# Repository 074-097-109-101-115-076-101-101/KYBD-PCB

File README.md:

# KYBD-PCB

### • ATMEGA32U4-AUR
### • Adafruit 5050 RGB LED with Integrated Driver Chip
### • USB C Port
### • Rotary Encoder
### • SRVO5-4
### • OLED Display
### • Crystal Oscillator

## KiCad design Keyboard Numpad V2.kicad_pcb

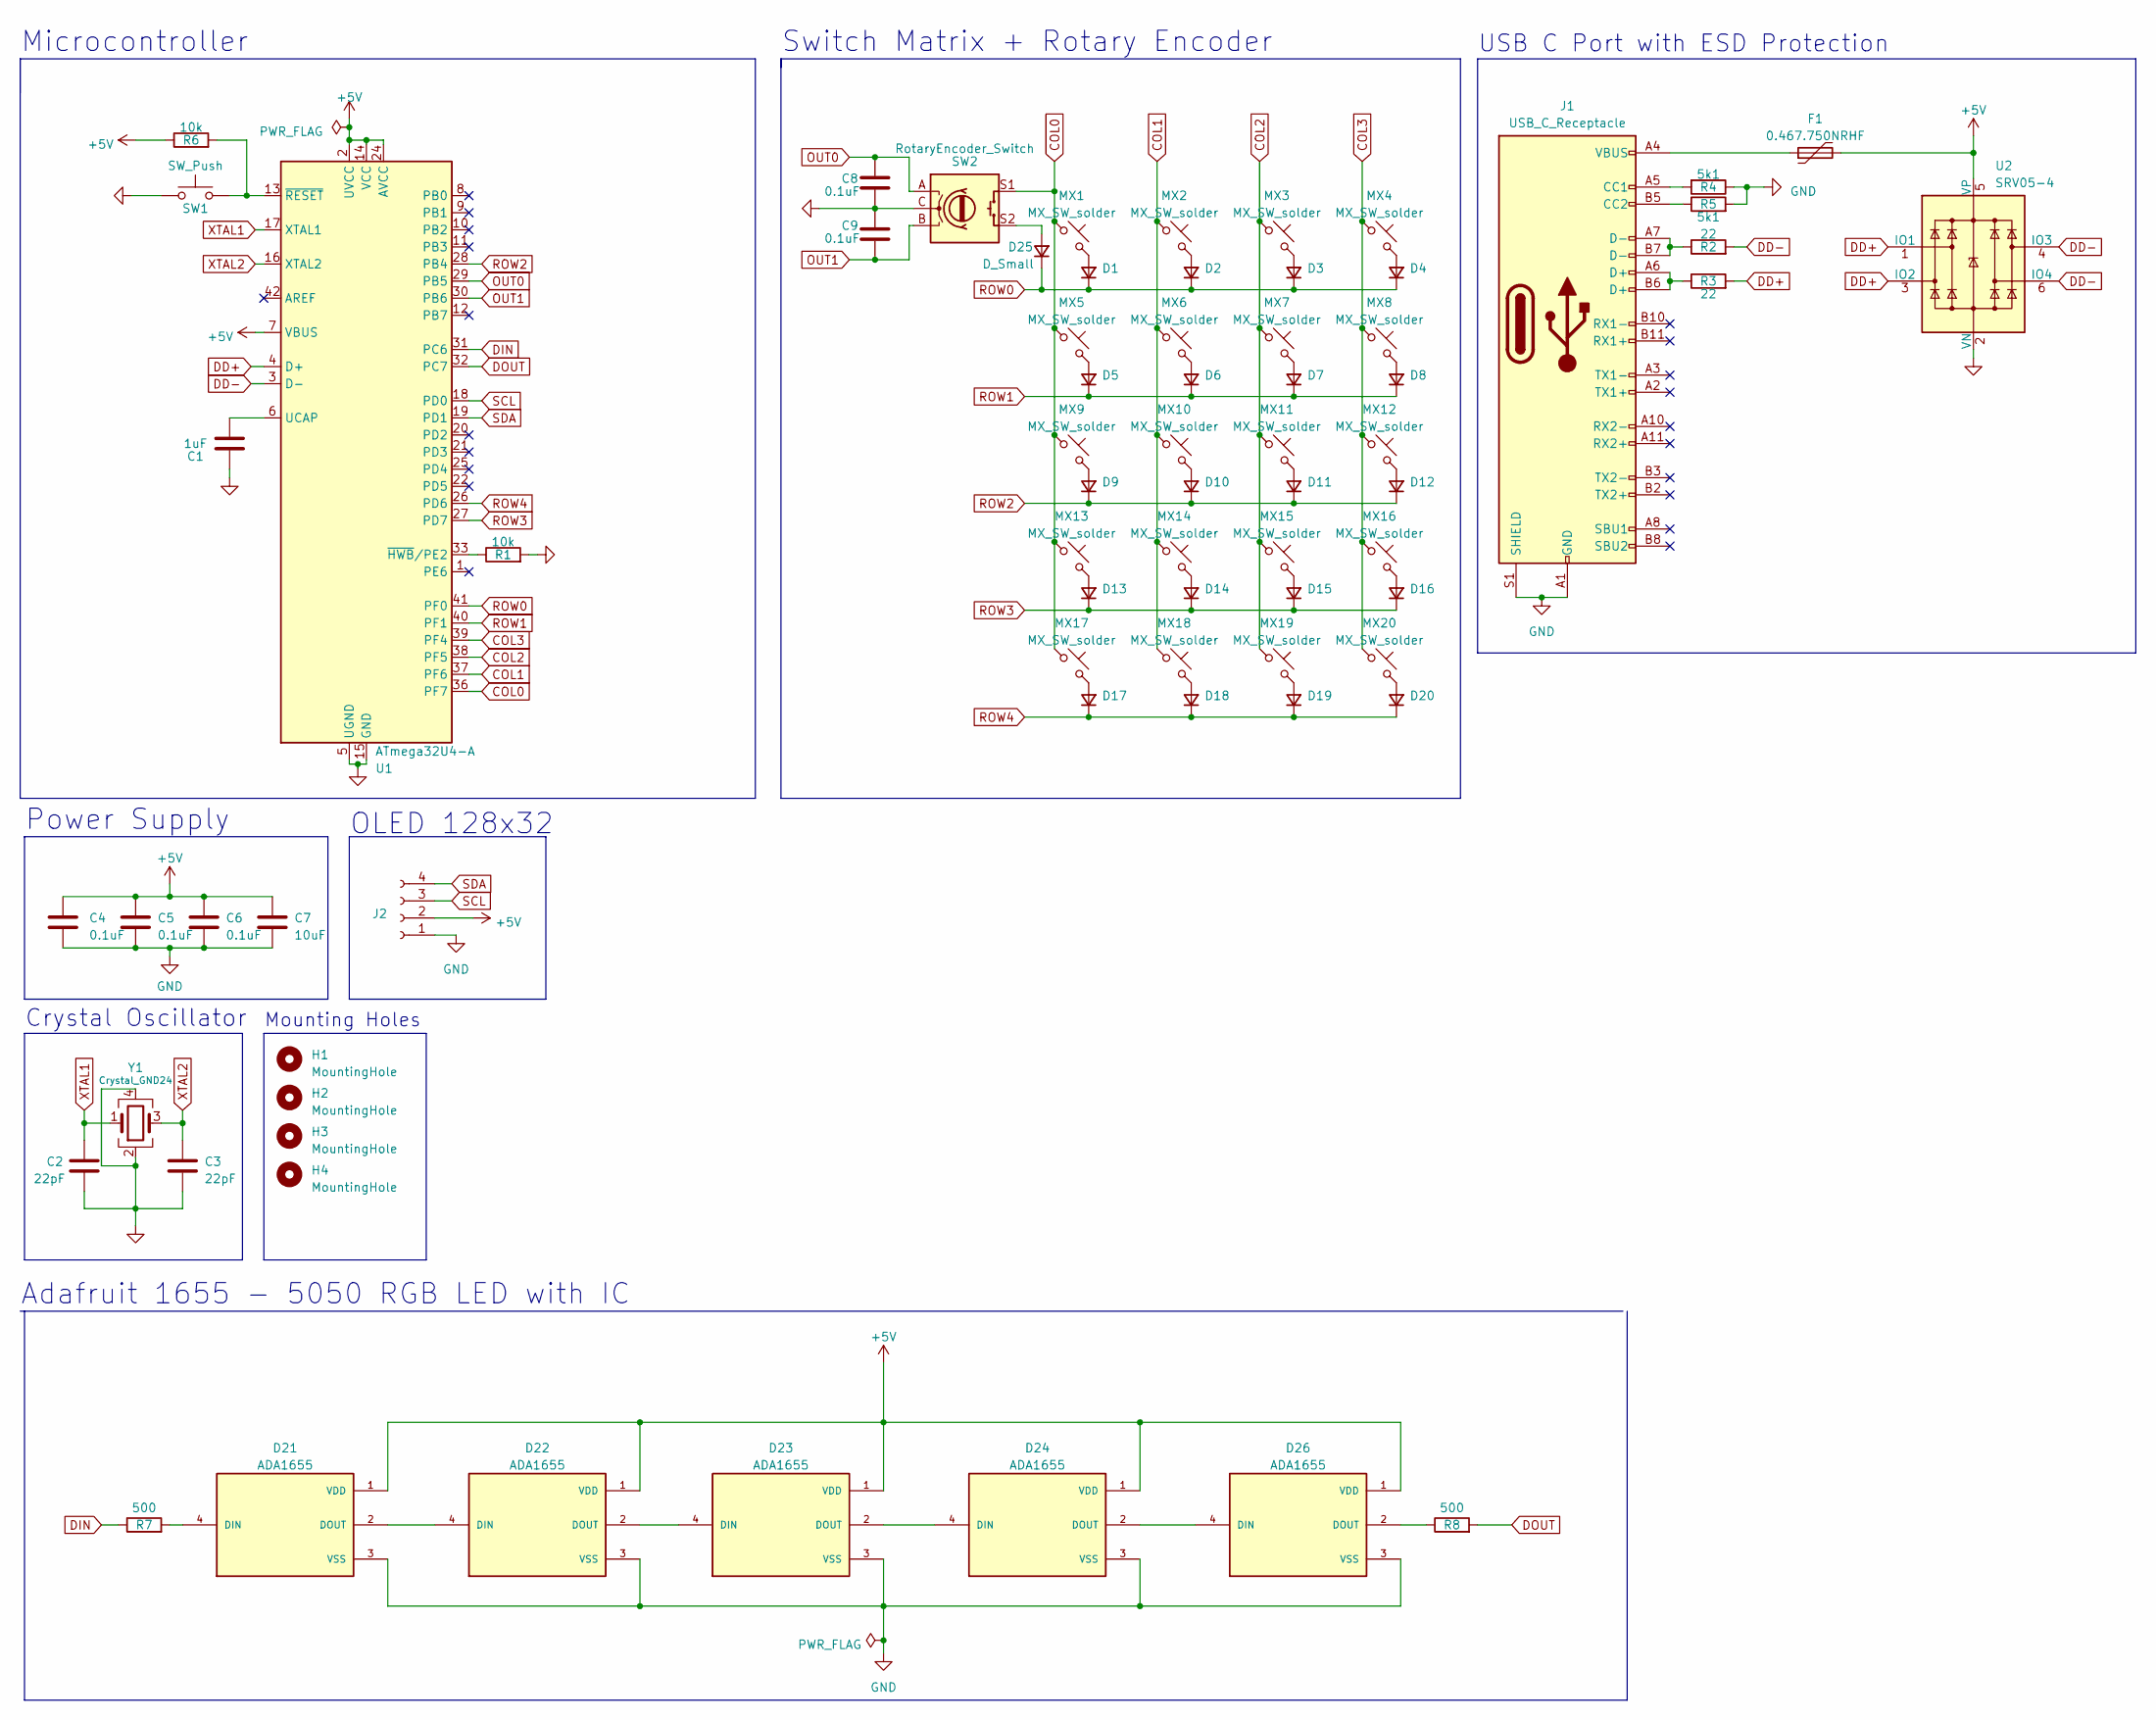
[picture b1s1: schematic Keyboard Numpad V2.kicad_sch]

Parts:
C1: 1uF; C_0805_2012Metric
C2, C3: 22pF; C_0805_2012Metric
C4, C5, C6, C8, C9: 0.1uF; C_0805_2012Metric
C7: 10uF; C_0805_2012Metric
D1, D2, D3, D4, D5, D6, D7, D8, D9, D10, D11, D12, D13, D14, D15, D16, D17, D18, D19, D20, D25: D_Small; D_SOD-123
D21, D22, D23, D24, D26: ADA1655; LED_ADA1655; PARTREV N/A
F1: 0.467.750NRHF; Fuse_0603_1608Metric
H1, H2, H3, H4: MountingHole; MountingHole_2.5mm
J1: USB_C_Receptacle; USB_C_Receptacle_Amphenol_12401610E4-2A
J2: Conn_01x04_Socket; SULLINS_PPTC041LFBN-RC
MX1, MX2, MX3, MX4, MX5, MX6, MX7, MX8, MX9, MX10, MX11, MX12, MX13, MX14, MX15, MX16, MX17, MX18, MX19, MX20: MX_SW_solder; SW_MX_1u
R1, R6: 10k; R_0805_2012Metric
R2, R3: 22; R_0805_2012Metric
R4, R5: 5k1; R_0805_2012Metric
R7, R8: 500; R_Axial_DIN0204_L3.6mm_D1.6mm_P5.08mm_Horizontal
SW1: SW_Push; SW_SPST_TL3342
SW2: RotaryEncoder_Switch; XDCR_PEC11R-4215F-S0024
U1: ATmega32U4-A; TQFP-44_10x10mm_P0.8mm
U2: SRV05-4; SOT-23-6
Y1: Crystal_GND24; Crystal_SMD_SeikoEpson_TSX3225-4Pin_3.2x2.5mm

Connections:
+5V: C4.1, C5.1, C6.1, C7.1, D21.1 (VDD), D22.1 (VDD), D23.1 (VDD), D24.1 (VDD), D26.1 (VDD), F1.2, J2.2, R6.1, U1.2 (UVCC), U1.7 (VBUS), U1.14 (VCC), U1.24 (AVCC), U1.34 (VCC), U1.44 (AVCC), U2.5 (VP)
COL0: MX1.1, MX5.1, MX9.1, MX13.1, MX17.1, SW2.S1, U1.36 (PF7)
COL1: MX2.1, MX6.1, MX10.1, MX14.1, MX18.1, U1.37 (PF6)
COL2: MX3.1, MX7.1, MX11.1, MX15.1, MX19.1, U1.38 (PF5)
COL3: MX4.1, MX8.1, MX12.1, MX16.1, MX20.1, U1.39 (PF4)
DD+: R3.2, U1.4 (D+), U2.1 (IO1), U2.3 (IO2)
DD-: R2.2, U1.3 (D-), U2.4 (IO3), U2.6 (IO4)
DIN: R7.1, U1.31 (PC6)
DOUT: R8.2, U1.32 (PC7)
GND: C1.2, C2.2, C3.2, C4.2, C5.2, C6.2, C7.2, C8.2, C9.1, D21.3 (VSS), D22.3 (VSS), D23.3 (VSS), D24.3 (VSS), D26.3 (VSS), J1.A1 (GND), J1.A12 (GND), J1.B1 (GND), J1.B12 (GND), J1.S1 (SHIELD), J2.1, R1.2, R4.1, R5.2, SW1.1, SW2.C, U1.5 (UGND), U1.15 (GND), U1.23 (GND), U1.35 (GND), U1.43 (GND), U2.2 (VN), Y1.2, Y1.4
unnamed: D1.2 (A), MX1.2
unnamed: D2.2 (A), MX2.2
unnamed: D3.2 (A), MX3.2
unnamed: D4.2 (A), MX4.2
unnamed: D5.2 (A), MX5.2
unnamed: D6.2 (A), MX6.2
unnamed: D7.2 (A), MX7.2
unnamed: D8.2 (A), MX8.2
unnamed: D9.2 (A), MX9.2
unnamed: D10.2 (A), MX10.2
unnamed: D11.2 (A), MX11.2
unnamed: D12.2 (A), MX12.2
unnamed: D13.2 (A), MX13.2
unnamed: D14.2 (A), MX14.2
unnamed: D15.2 (A), MX15.2
unnamed: D16.2 (A), MX16.2
unnamed: D17.2 (A), MX17.2
unnamed: D18.2 (A), MX18.2
unnamed: D19.2 (A), MX19.2
unnamed: D20.2 (A), MX20.2
unnamed: D21.4 (DIN), R7.2
unnamed: D21.2 (DOUT), D22.4 (DIN)
unnamed: D22.2 (DOUT), D23.4 (DIN)
unnamed: D23.2 (DOUT), D24.4 (DIN)
unnamed: D24.2 (DOUT), D26.4 (DIN)
unnamed: D25.2 (A), SW2.S2
unnamed: D26.2 (DOUT), R8.1
unnamed: F1.1, J1.A4 (VBUS), J1.A9 (VBUS), J1.B4 (VBUS), J1.B9 (VBUS)
unnamed: J1.A5 (CC1), R4.2
unnamed: J1.B5 (CC2), R5.1
unnamed: J1.A6 (D+), J1.B6 (D+), R3.1
unnamed: J1.A7 (D-), J1.B7 (D-), R2.1
unnamed: C1.1, U1.6 (UCAP)
unnamed: R1.1, U1.33 (~HWB/PE2)
unnamed: R6.2, SW1.2, U1.13 (~RESET)
OUT0: C8.1, SW2.A, U1.29 (PB5)
OUT1: C9.2, SW2.B, U1.30 (PB6)
ROW0: D1.1 (K), D2.1 (K), D3.1 (K), D4.1 (K), D25.1 (K), U1.41 (PF0)
ROW1: D5.1 (K), D6.1 (K), D7.1 (K), D8.1 (K), U1.40 (PF1)
ROW2: D9.1 (K), D10.1 (K), D11.1 (K), D12.1 (K), U1.28 (PB4)
ROW3: D13.1 (K), D14.1 (K), D15.1 (K), D16.1 (K), U1.27 (PD7)
ROW4: D17.1 (K), D18.1 (K), D19.1 (K), D20.1 (K), U1.26 (PD6)
SCL: J2.3, U1.18 (PD0)
SDA: J2.4, U1.19 (PD1)
XTAL1: C2.1, U1.17 (XTAL1), Y1.1
XTAL2: C3.1, U1.16 (XTAL2), Y1.3

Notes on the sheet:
OLED 128x32
Switch Matrix + Rotary Encoder
Crystal Oscillator
Adafruit 1655 - 5050 RGB LED with IC
Microcontroller
Mounting Holes
Power Supply
USB C Port with ESD Protection

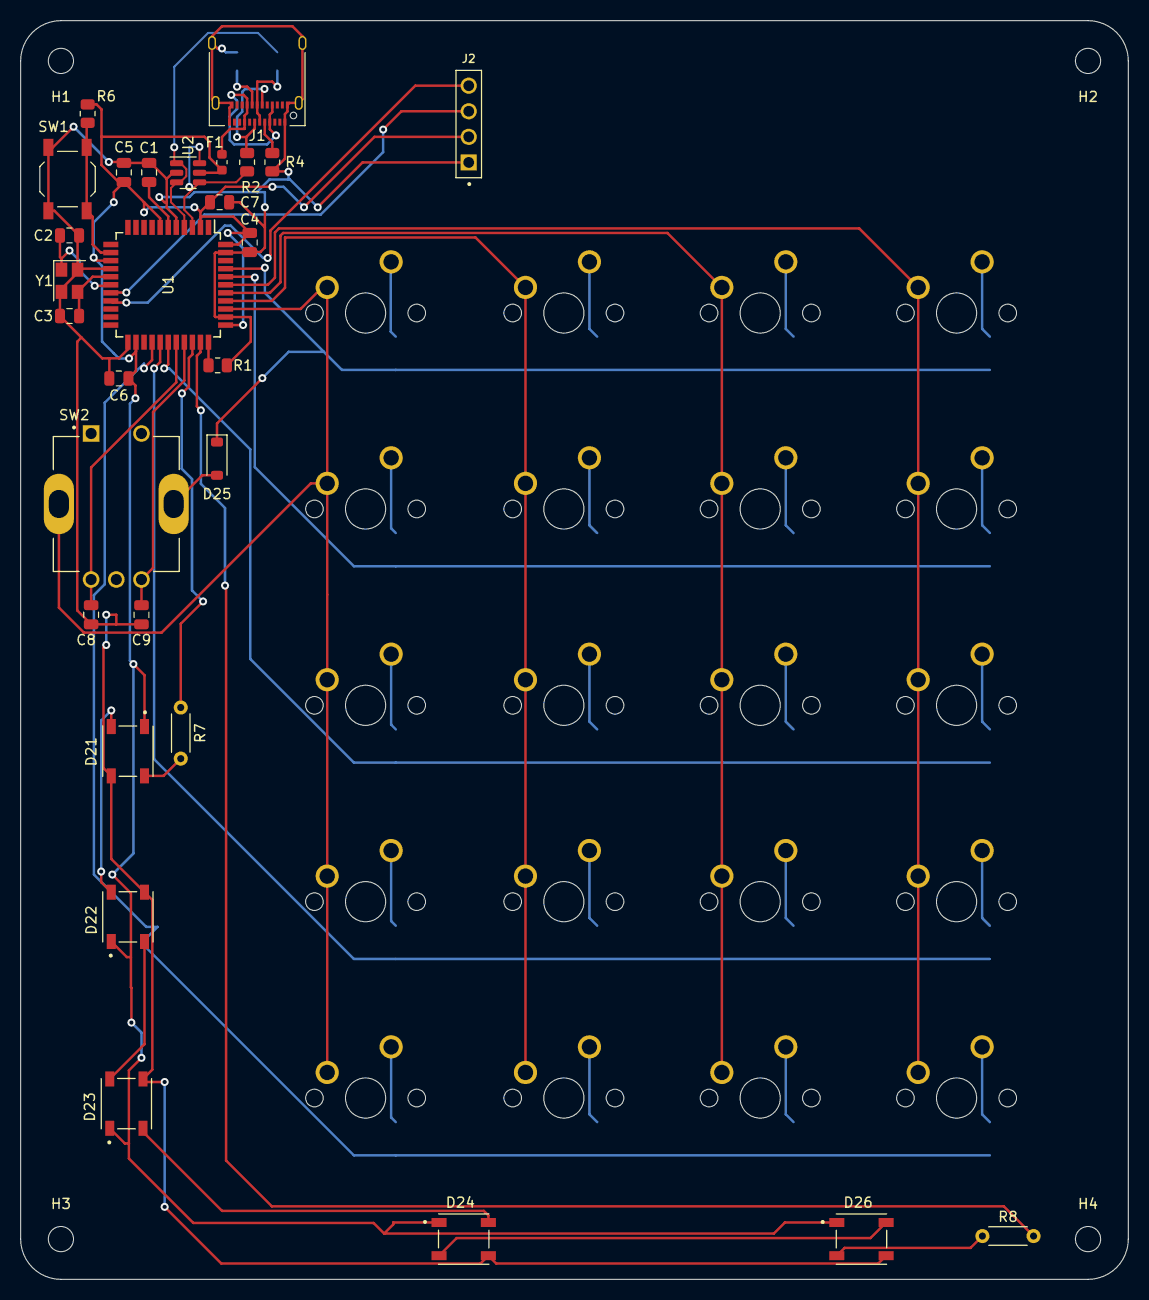
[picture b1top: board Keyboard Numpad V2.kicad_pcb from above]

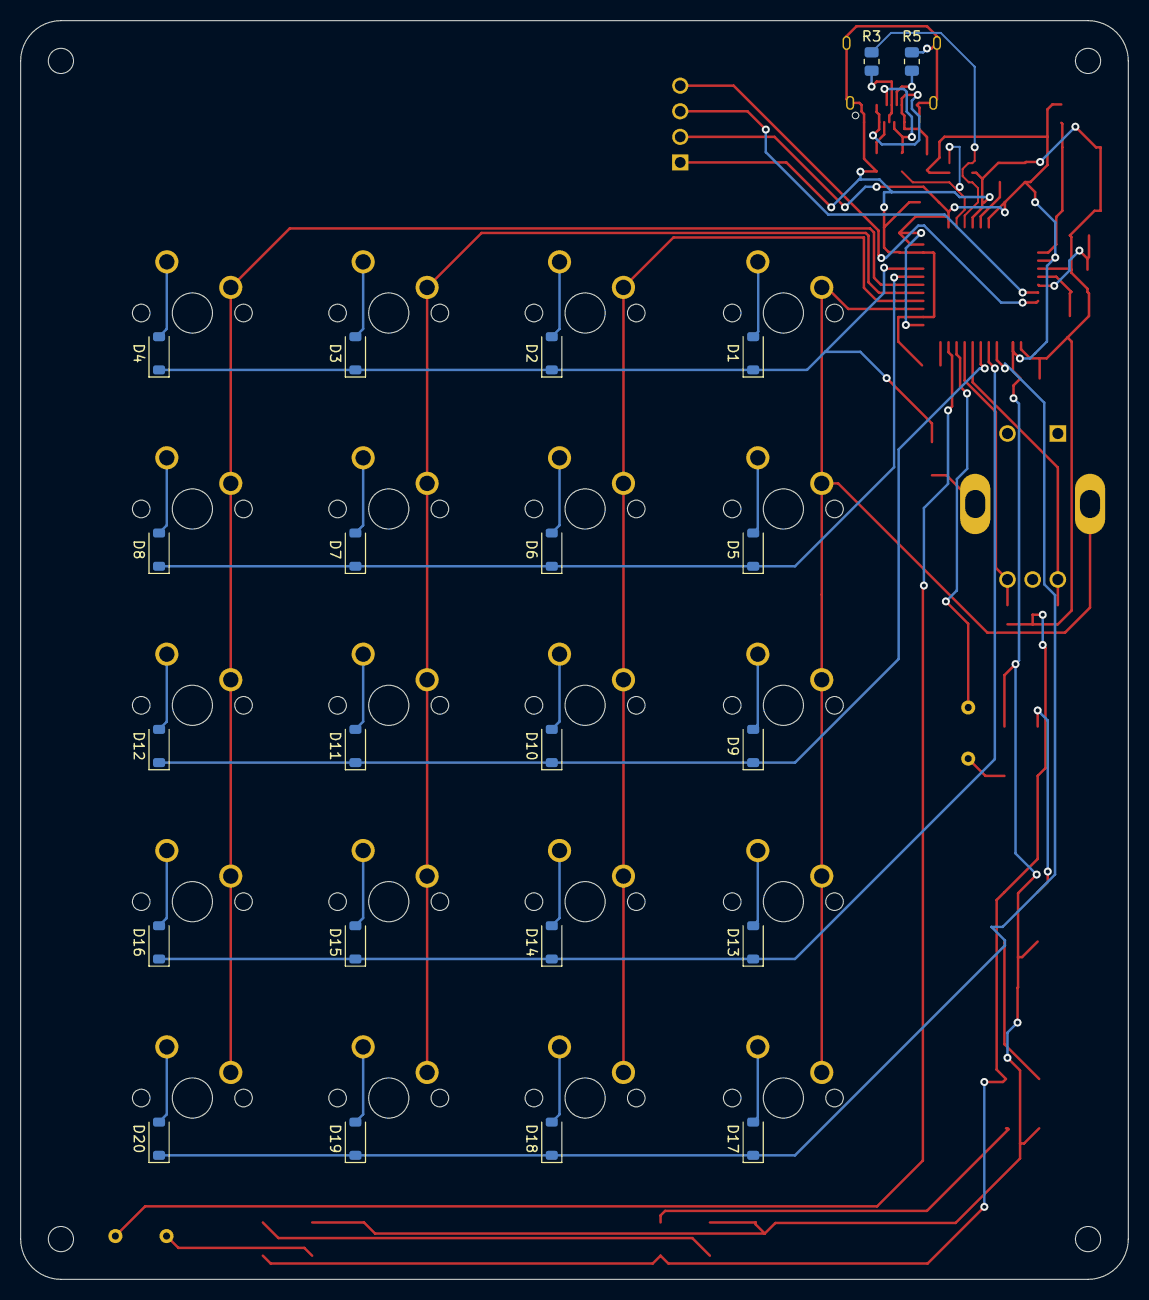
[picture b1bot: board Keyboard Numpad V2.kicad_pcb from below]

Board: 2 copper layers, 110.0 x 125.0 mm, 75 parts (22 on the bottom side), 56 nets.

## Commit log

2023-05-26 Create Libraries
2023-05-26 Create E
